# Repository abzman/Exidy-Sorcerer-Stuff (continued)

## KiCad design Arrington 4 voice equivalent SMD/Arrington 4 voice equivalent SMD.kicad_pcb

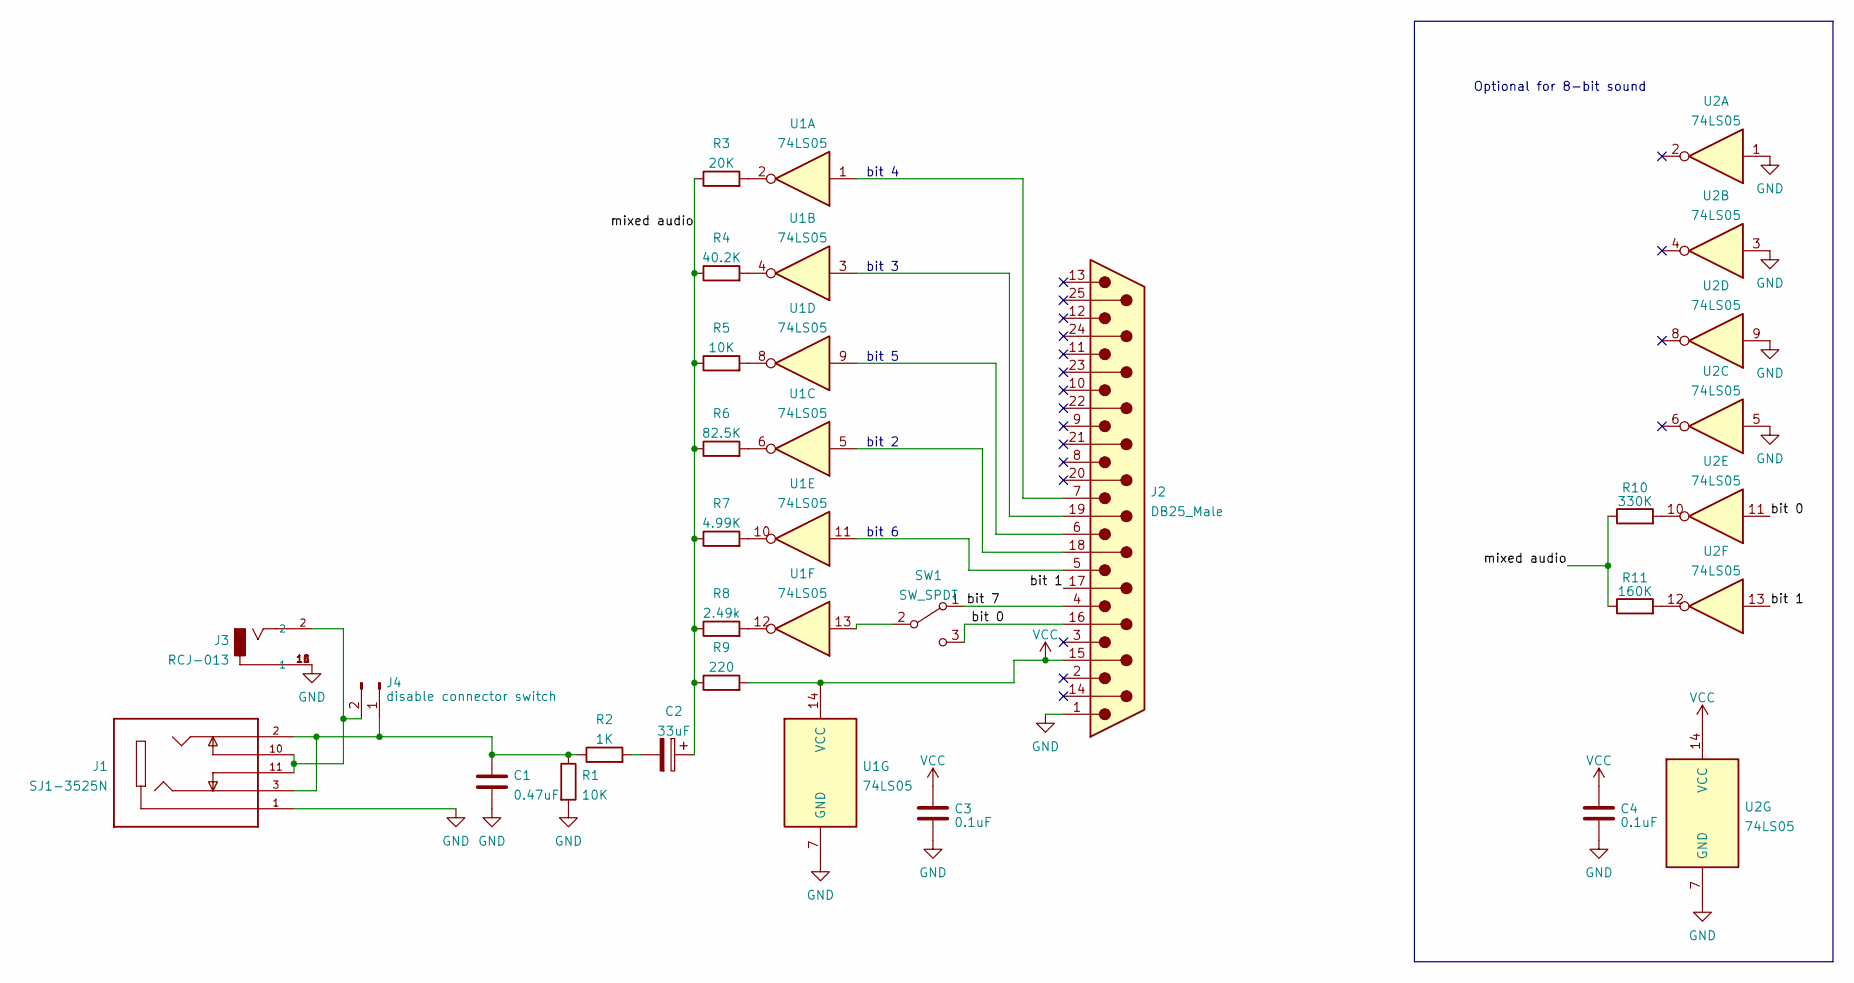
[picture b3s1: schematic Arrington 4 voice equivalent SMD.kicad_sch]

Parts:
C1: 0.47uF; C_0603_1608Metric
C2: 33uF; CP_Radial_D5.0mm_P2.00mm
C3, C4: 0.1uF; C_0603_1608Metric
J1: SJ1-3525N; CUI_SJ1-3525N; PARTREV 1.02
J2: DB25_Male; DSUB-25_Male_EdgeMount_P2.77mm
J3: RCJ-013; CUI_RCJ-013; PART_REV B
J4: disable connector switch; PinHeader_1x02_P2.54mm_Vertical
R1, R5: 10K; R_0603_1608Metric
R2: 1K; R_0603_1608Metric
R3: 20K; R_0603_1608Metric
R4: 40.2K; R_0603_1608Metric
R6: 82.5K; R_0603_1608Metric
R7: 4.99K; R_0603_1608Metric
R8: 2.49k; R_0603_1608Metric
R9: 220; R_0603_1608Metric
R10: 330K; R_0603_1608Metric
R11: 160K; R_0603_1608Metric
SW1: SW_SPDT; PinHeader_1x03_P2.54mm_Vertical
U1, U2: 74LS05; SO-14_3.9x8.65mm_P1.27mm

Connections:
/bit 0: J2.16, SW1.3 (C), U2.11
/bit 1: J2.17, U2.13
/bit 7: J2.4, SW1.1 (A)
/mixed audio: C2.1, R3.1, R4.1, R5.1, R6.1, R7.1, R8.1, R9.1, R10.1, R11.1
GND: C1.2, C3.2, C4.2, J1.1, J2.1, J3.1A (1), J3.1B (1), J3.1C (1), R1.2, U1.7 (GND), U2.1, U2.3, U2.5, U2.7 (GND), U2.9
unnamed: C2.2, R2.2
unnamed: J2.18, U1.5
unnamed: J2.19, U1.3
unnamed: J2.5, U1.11
unnamed: J2.6, U1.9
unnamed: J2.7, U1.1
unnamed: C1.1, J1.2, J1.3, J4.1, R1.1, R2.1
unnamed: J1.10, J1.11, J3.2, J4.2
unnamed: R3.2, U1.2
unnamed: R4.2, U1.4
unnamed: R5.2, U1.8
unnamed: R6.2, U1.6
unnamed: R7.2, U1.10
unnamed: R8.2, U1.12
unnamed: R10.2, U2.10
unnamed: R11.2, U2.12
unnamed: SW1.2 (B), U1.13
VCC: C3.1, C4.1, J2.15, R9.2, U1.14 (VCC), U2.14 (VCC)

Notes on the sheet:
Optional for 8-bit sound
bit 2
bit 5
bit 4
bit 6
bit 3

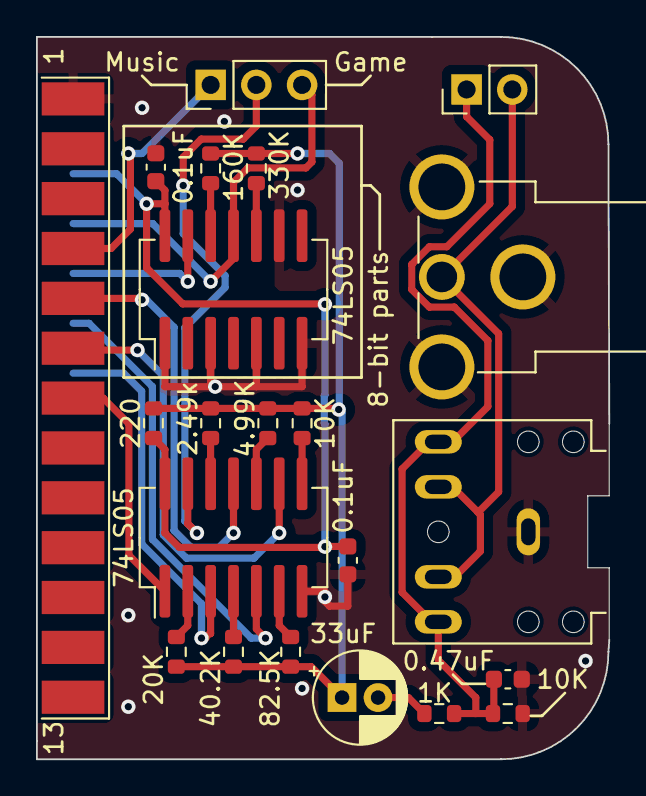
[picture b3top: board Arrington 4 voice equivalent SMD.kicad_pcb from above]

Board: 2 copper layers, 31.8 x 40.1 mm, 22 parts (0 on the bottom side), 23 nets.

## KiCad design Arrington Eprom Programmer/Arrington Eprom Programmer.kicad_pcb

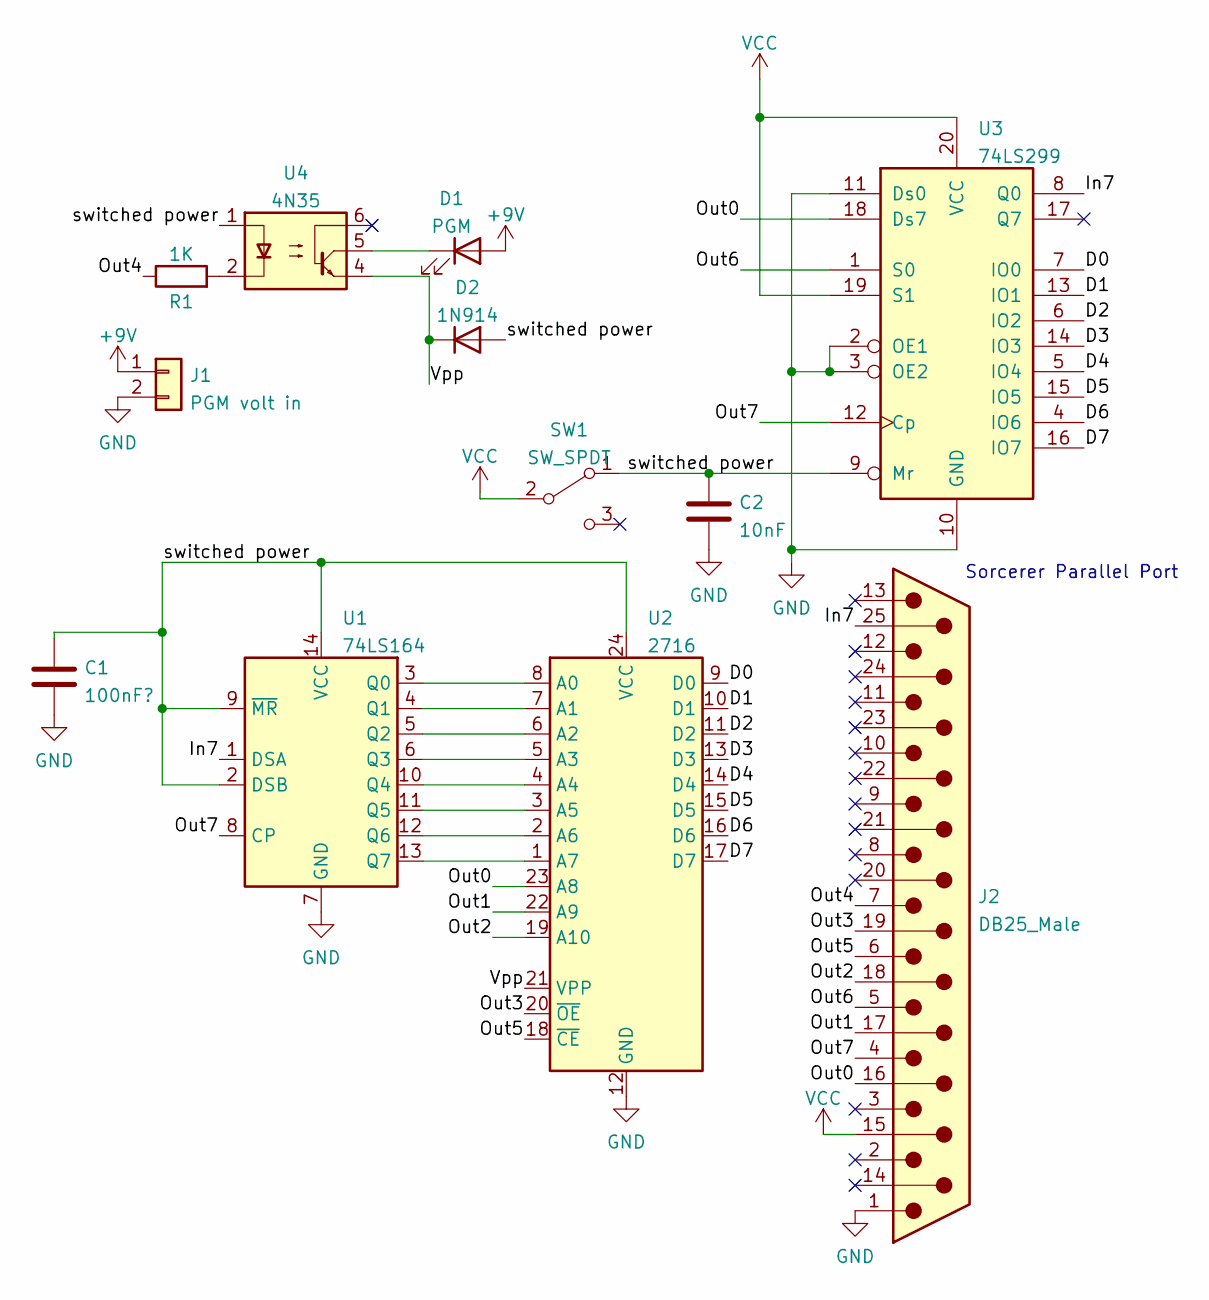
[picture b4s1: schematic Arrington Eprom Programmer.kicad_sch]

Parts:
C1: 100nF?; C_Rect_L9.0mm_W2.5mm_P7.50mm_MKT
C2: 10nF; C_Rect_L9.0mm_W2.5mm_P7.50mm_MKT
D1: PGM; LED_D3.0mm
D2: 1N914; D_DO-35_SOD27_P7.62mm_Horizontal
J1: PGM volt in; PinHeader_1x02_P2.54mm_Vertical
J2: DB25_Male; DSUB-25_Male_EdgeMount_P2.77mm
R1: 1K; R_Axial_DIN0207_L6.3mm_D2.5mm_P10.16mm_Horizontal
SW1: SW_SPDT; PinHeader_1x03_P2.54mm_Vertical
U1: 74LS164; DIP-14_W7.62mm
U2: 2716; DIP-24_W15.24mm
U3: 74LS299; DIP-20_W7.62mm
U4: 4N35; DIP-6_W7.62mm

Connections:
+9V: D1.2 (A), J1.1
/D0: U2.9 (D0), U3.7 (IO0)
/D1: U2.10 (D1), U3.13 (IO1)
/D2: U2.11 (D2), U3.6 (IO2)
/D3: U2.13 (D3), U3.14 (IO3)
/D4: U2.14 (D4), U3.5 (IO4)
/D5: U2.15 (D5), U3.15 (IO5)
/D6: U2.16 (D6), U3.4 (IO6)
/D7: U2.17 (D7), U3.16 (IO7)
/In7: J2.25, U1.1 (DSA), U3.8 (Q0)
/Out0: J2.16, U2.23 (A8), U3.18 (Ds7)
/Out1: J2.17, U2.22 (A9)
/Out2: J2.18, U2.19 (A10)
/Out3: J2.19, U2.20 (~OE)
/Out4: J2.7, R1.1
/Out5: J2.6, U2.18 (~CE)
/Out6: J2.5, U3.1 (S0)
/Out7: J2.4, U1.8 (CP), U3.12 (Cp)
/Vpp: D2.1 (K), U2.21 (VPP), U4.4
/switched power: C1.1, C2.1, D2.2 (A), SW1.1 (A), U1.2 (DSB), U1.9 (~MR), U1.14 (VCC), U2.24 (VCC), U3.9 (Mr), U4.1
GND: C1.2, C2.2, J1.2, J2.1, U1.7 (GND), U2.12 (GND), U3.2 (OE1), U3.3 (OE2), U3.10 (GND), U3.11 (Ds0)
unnamed: D1.1 (K), U4.5
unnamed: R1.2, U4.2
unnamed: U1.3 (Q0), U2.8 (A0)
unnamed: U1.4 (Q1), U2.7 (A1)
unnamed: U1.5 (Q2), U2.6 (A2)
unnamed: U1.6 (Q3), U2.5 (A3)
unnamed: U1.10 (Q4), U2.4 (A4)
unnamed: U1.11 (Q5), U2.3 (A5)
unnamed: U1.12 (Q6), U2.2 (A6)
unnamed: U1.13 (Q7), U2.1 (A7)
VCC: J2.15, SW1.2 (B), U3.19 (S1), U3.20 (VCC)

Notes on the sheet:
Sorcerer Parallel Port

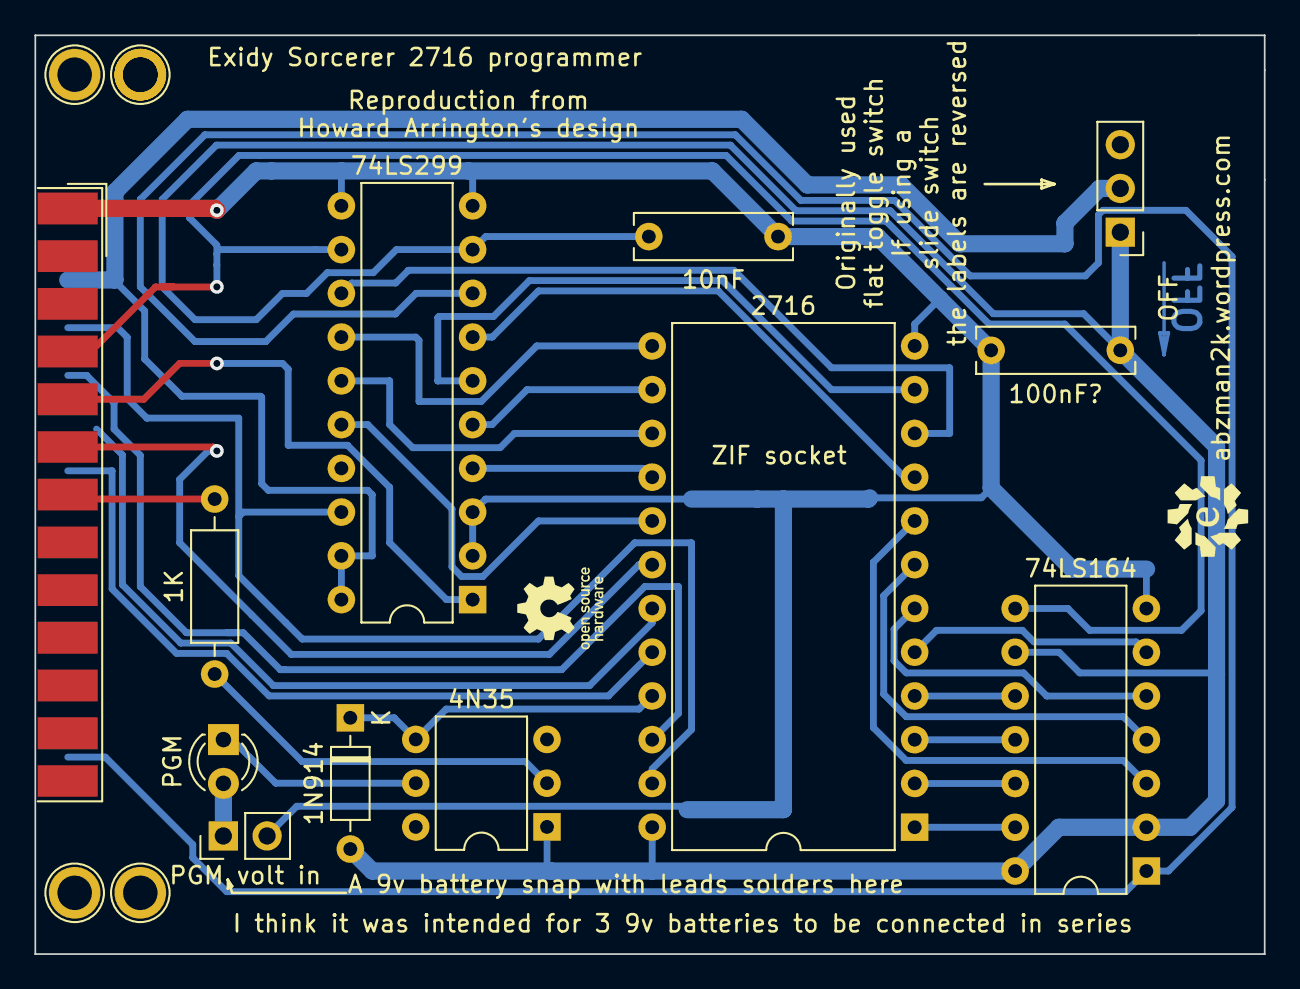
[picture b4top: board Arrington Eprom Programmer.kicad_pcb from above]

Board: 2 copper layers, 71.4 x 53.3 mm, 12 parts (0 on the bottom side), 32 nets.

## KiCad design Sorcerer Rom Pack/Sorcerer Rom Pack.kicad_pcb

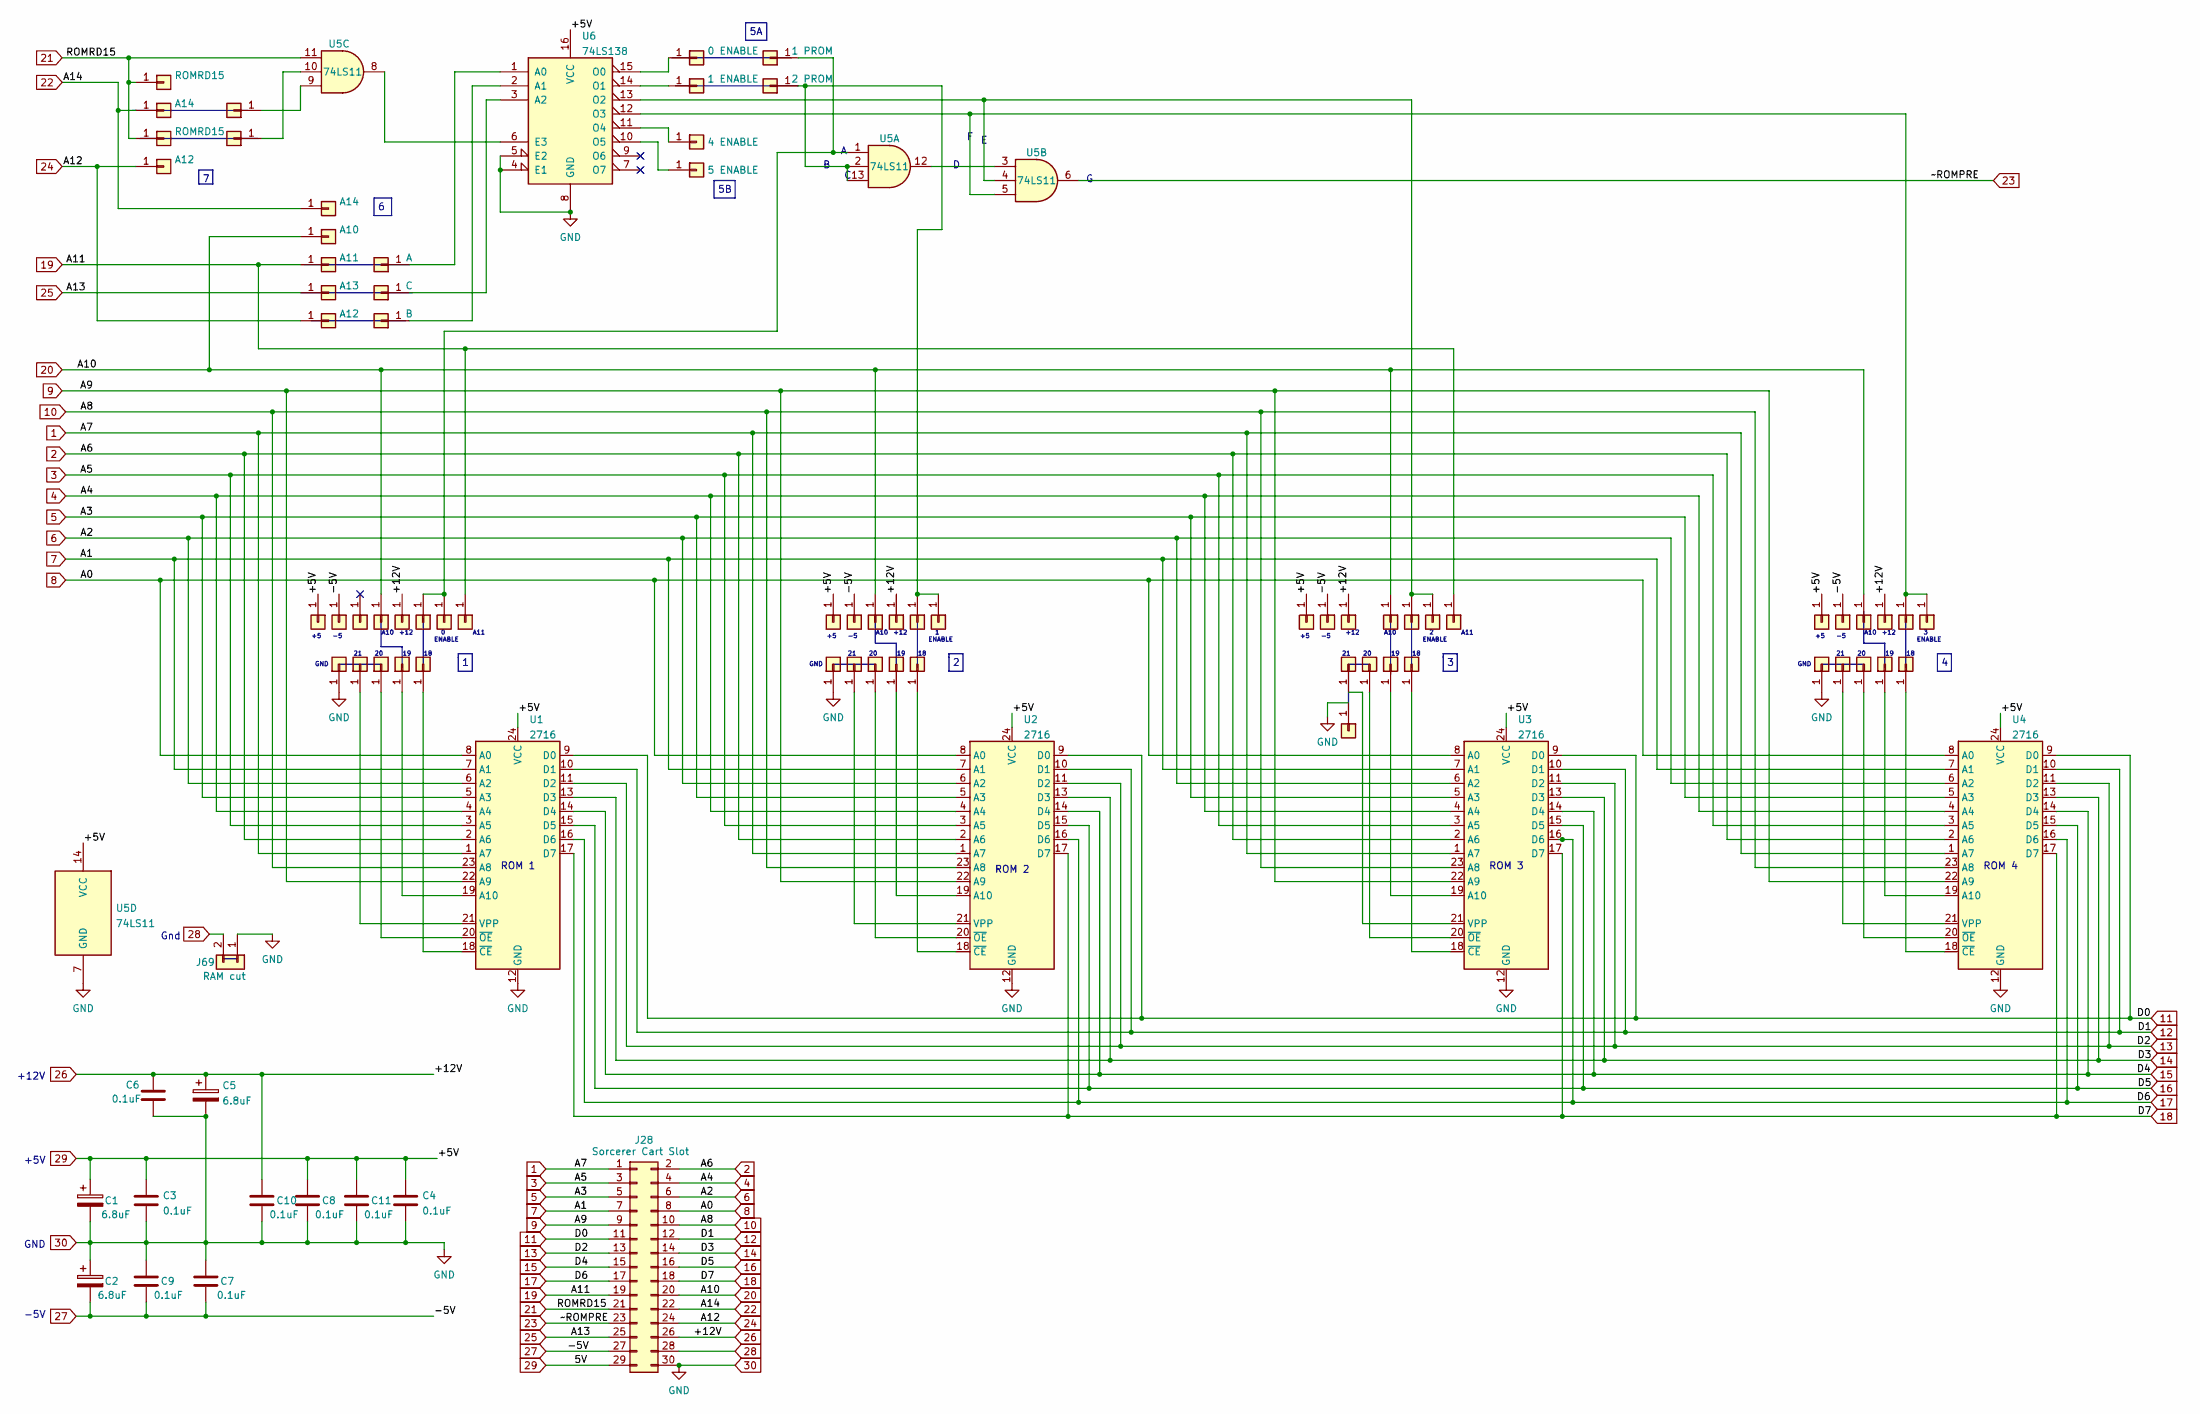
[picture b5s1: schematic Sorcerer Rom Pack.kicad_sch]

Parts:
C1, C2, C5: 6.8uF; CP_Radial_Tantal_D4.5mm_P5.00mm
C3, C4, C6, C7, C8, C9, C10, C11: 0.1uF; C_Disc_D4.3mm_W1.9mm_P5.00mm
J1, J3: ROMRD15; PinHeader_1x01_P2.54mm_Vertical
J2, J8: A14; PinHeader_1x01_P2.54mm_Vertical
J4, J12: A12; PinHeader_1x01_P2.54mm_Vertical
J5, J6: Conn_01x01; PinHeader_1x01_P2.54mm_Vertical
J7, J13, J14, J15, J16, J17, J20, J21, J22, J23, J24, J25, J26, J27, J35, J36, J37, J38, J39, J40, J41, J42, J43, J44, J45, J46, J47, J48, J49, J50, J51, J52, J53, J54, J55, J56, J57, J58, J59, J60, J61, J62, J63, J64, J65, J66, J67, J68: A; PinHeader_1x01_P2.54mm_Vertical
J9: A10; PinHeader_1x01_P2.54mm_Vertical
J10: A11; PinHeader_1x01_P2.54mm_Vertical
J11: A13; PinHeader_1x01_P2.54mm_Vertical
J18: C; PinHeader_1x01_P2.54mm_Vertical
J19: B; PinHeader_1x01_P2.54mm_Vertical
J28: Sorcerer Cart Slot; edge mounted 30 pin card edge connector (2x15 pin)
J29: 0 ENABLE; PinHeader_1x01_P2.54mm_Vertical
J30: 1 ENABLE; PinHeader_1x01_P2.54mm_Vertical
J31: 4 ENABLE; PinHeader_1x01_P2.54mm_Vertical
J32: 5 ENABLE; PinHeader_1x01_P2.54mm_Vertical
J33: 1 PROM; PinHeader_1x01_P2.54mm_Vertical
J34: 2 PROM; PinHeader_1x01_P2.54mm_Vertical
J69: RAM cut; SolderJumper-2_P1.3mm_Open_RoundedPad1.0x1.5mm
U1, U2, U3, U4: 2716; DIP-24_W15.24mm
U5: 74LS11; DIP-14_W7.62mm
U6: 74LS138; DIP-16_W7.62mm

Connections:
1: J28.1, U1.1 (A7), U2.1 (A7), U3.1 (A7), U4.1 (A7)
2: J28.2, U1.2 (A6), U2.2 (A6), U3.2 (A6), U4.2 (A6)
3: J28.3, U1.3 (A5), U2.3 (A5), U3.3 (A5), U4.3 (A5)
4: J28.4, U1.4 (A4), U2.4 (A4), U3.4 (A4), U4.4 (A4)
5: J28.5, U1.5 (A3), U2.5 (A3), U3.5 (A3), U4.5 (A3)
6: J28.6, U1.6 (A2), U2.6 (A2), U3.6 (A2), U4.6 (A2)
7: J28.7, U1.7 (A1), U2.7 (A1), U3.7 (A1), U4.7 (A1)
8: J28.8, U1.8 (A0), U2.8 (A0), U3.8 (A0), U4.8 (A0)
9: J28.9, U1.22 (A9), U2.22 (A9), U3.22 (A9), U4.22 (A9)
10: J28.10, U1.23 (A8), U2.23 (A8), U3.23 (A8), U4.23 (A8)
11: J28.11, U1.9 (D0), U2.9 (D0), U3.9 (D0), U4.9 (D0)
12: J28.12, U1.10 (D1), U2.10 (D1), U3.10 (D1), U4.10 (D1)
13: J28.13, U1.11 (D2), U2.11 (D2), U3.11 (D2), U4.11 (D2)
14: J28.14, U1.13 (D3), U2.13 (D3), U3.13 (D3), U4.13 (D3)
15: J28.15, U1.14 (D4), U2.14 (D4), U3.14 (D4), U4.14 (D4)
16: J28.16, U1.15 (D5), U2.15 (D5), U3.15 (D5), U4.15 (D5)
17: J28.17, U1.16 (D6), U2.16 (D6), U3.16 (D6), U4.16 (D6)
18: J28.18, U1.17 (D7), U2.17 (D7), U3.17 (D7), U4.17 (D7)
19: J10.1, J27.1, J28.19, J57.1
20: J9.1, J20.1, J28.20, J39.1, J52.1, J62.1
21: J1.1, J3.1, J28.21, U5.11
22: J2.1, J8.1, J28.22
23: J28.23, U5.6
24: J4.1, J12.1, J28.24
25: J11.1, J28.25
26: C5.1, C6.1, C10.1, J22.1, J28.26, J41.1, J48.1, J64.1
27: C2.2, C7.2, C9.2, J13.1, J28.27, J37.1, J47.1, J60.1
28: J28.28, J69.2
29: C1.1, C3.1, C4.1, C8.1, C11.1, J7.1, J28.29, J35.1, J46.1, J58.1, U1.24 (VCC), U2.24 (VCC), U3.24 (VCC), U4.24 (VCC), U5.14 (VCC), U6.16 (VCC)
30: C1.2, C2.1, C3.2, C4.2, C5.2, C6.2, C7.1, C8.2, C9.1, C10.2, C11.2, J14.1, J28.30, J36.1, J50.1, J59.1, J69.1, U1.12 (GND), U2.12 (GND), U3.12 (GND), U4.12 (GND), U5.7 (GND), U6.4 (E1), U6.5 (E2), U6.8 (GND)
unnamed: J5.1, U5.9
unnamed: J6.1, U5.10
unnamed: J16.1, U1.21 (VPP)
unnamed: J17.1, U6.1 (A0)
unnamed: J18.1, U6.3 (A2)
unnamed: J19.1, U6.2 (A1)
unnamed: J21.1, U1.20 (~OE)
unnamed: J23.1, U1.19 (A10)
unnamed: J24.1, J26.1, J33.1, U5.1
unnamed: J25.1, U1.18 (~CE)
unnamed: J29.1, U6.15 (O0)
unnamed: J30.1, U6.14 (O1)
unnamed: J31.1, U6.11 (O4)
unnamed: J32.1, U6.10 (O5)
unnamed: J34.1, J43.1, J45.1, U5.2, U5.13
unnamed: J38.1, U2.21 (VPP)
unnamed: J40.1, U2.20 (~OE)
unnamed: J42.1, U2.19 (A10)
unnamed: J44.1, U2.18 (~CE)
unnamed: J49.1, U3.21 (VPP)
unnamed: J51.1, U3.20 (~OE)
unnamed: J53.1, U3.19 (A10)
unnamed: J54.1, J56.1, U5.4, U6.13 (O2)
unnamed: J55.1, U3.18 (~CE)
unnamed: J61.1, U4.21 (VPP)
unnamed: J63.1, U4.20 (~OE)
unnamed: J65.1, U4.19 (A10)
unnamed: J66.1, J68.1, U5.5, U6.12 (O3)
unnamed: J67.1, U4.18 (~CE)
unnamed: U5.8, U6.6 (E3)
unnamed: U5.3, U5.12

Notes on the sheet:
+12
+5V
-5V
A11
0 ENABLE
A10
ROM 4
GND
1 ENABLE
Gnd
3 ENABLE
ROM 3
+12V
ROM 2
ROM 1
2 ENABLE

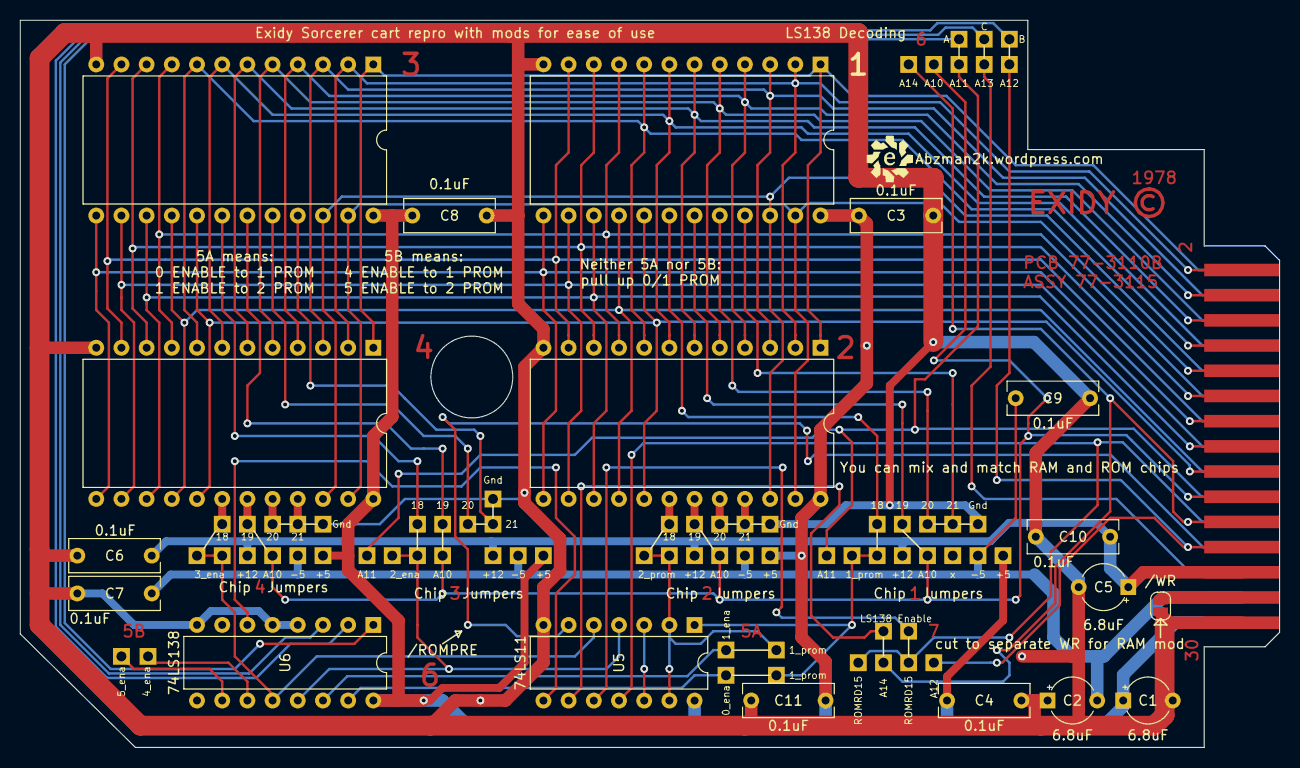
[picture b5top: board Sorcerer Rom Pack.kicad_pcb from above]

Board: 2 copper layers, 127.0 x 73.3 mm, 86 parts (0 on the bottom side), 61 nets.

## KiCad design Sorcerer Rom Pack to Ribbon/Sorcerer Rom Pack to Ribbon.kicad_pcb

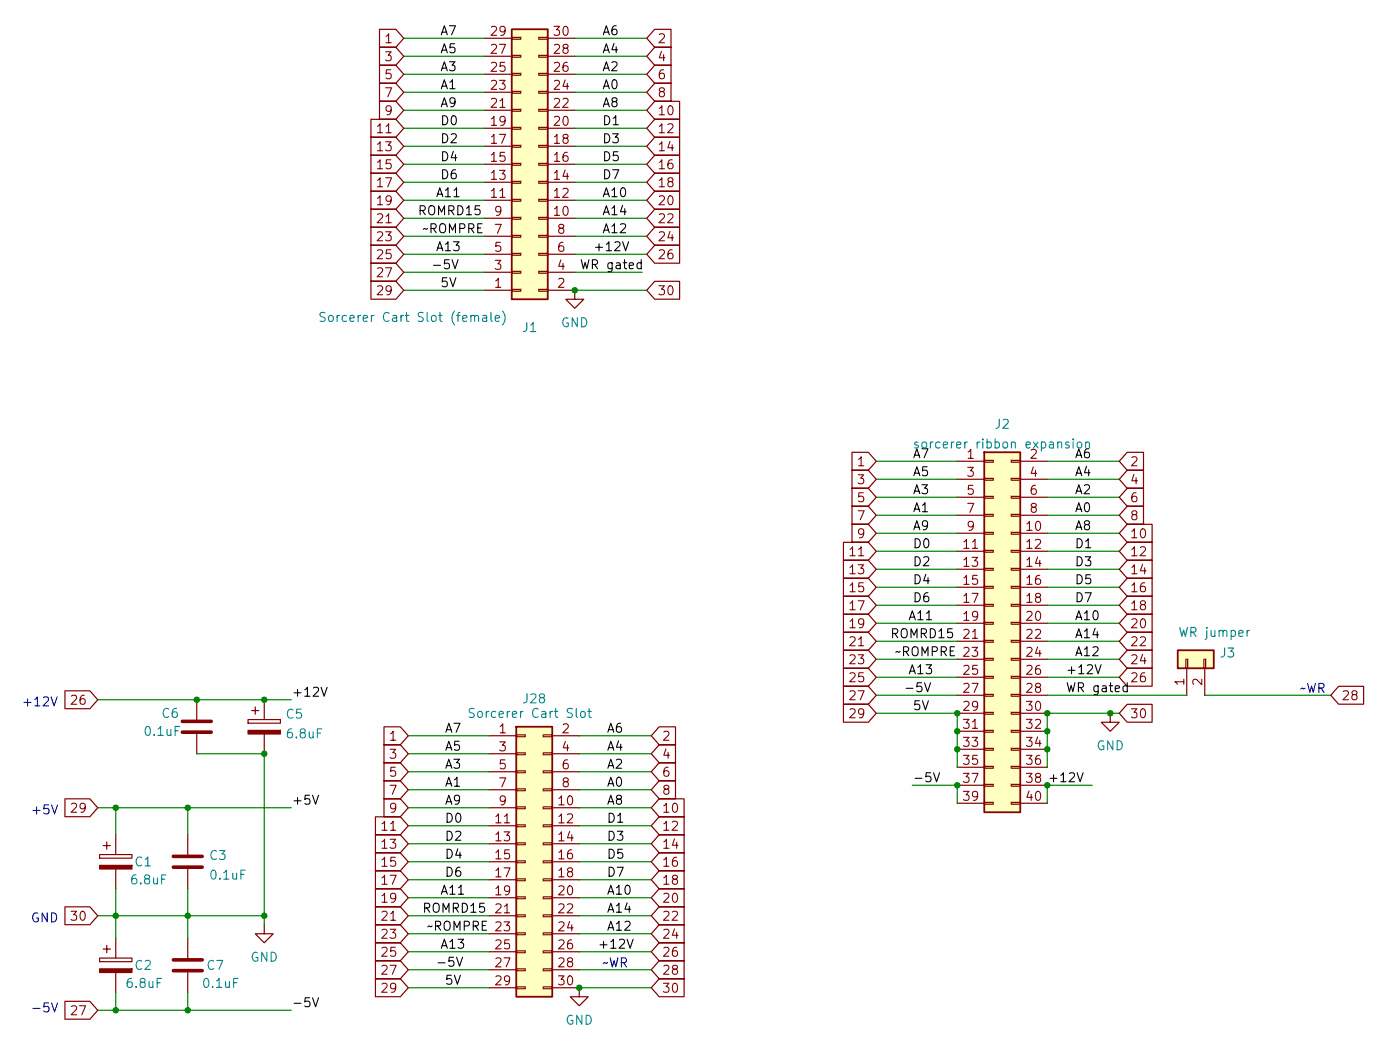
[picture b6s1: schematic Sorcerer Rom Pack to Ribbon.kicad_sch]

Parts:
C1, C2, C5: 6.8uF; CP_Radial_Tantal_D4.5mm_P5.00mm
C3, C6, C7: 0.1uF; C_Disc_D4.3mm_W1.9mm_P5.00mm
J1: Sorcerer Cart Slot (female); edge mounted 30 pin card edge connector (2x15 pin)
J2: sorcerer ribbon expansion; PinHeader_2x20_P2.54mm_Vertical
J3: WR jumper; SolderJumper-2_P1.3mm_Open_RoundedPad1.0x1.5mm
J28: Sorcerer Cart Slot; edge mounted 30 pin card edge connector (2x15 pin)

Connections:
1: J1.29, J2.1, J28.1
2: J1.30, J2.2, J28.2
3: J1.27, J2.3, J28.3
4: J1.28, J2.4, J28.4
5: J1.25, J2.5, J28.5
6: J1.26, J2.6, J28.6
7: J1.23, J2.7, J28.7
8: J1.24, J2.8, J28.8
9: J1.21, J2.9, J28.9
10: J1.22, J2.10, J28.10
11: J1.19, J2.11, J28.11
12: J1.20, J2.12, J28.12
13: J1.17, J2.13, J28.13
14: J1.18, J2.14, J28.14
15: J1.15, J2.15, J28.15
16: J1.16, J2.16, J28.16
17: J1.13, J2.17, J28.17
18: J1.14, J2.18, J28.18
19: J1.11, J2.19, J28.19
20: J1.12, J2.20, J28.20
21: J1.9, J2.21, J28.21
22: J1.10, J2.22, J28.22
23: J1.7, J2.23, J28.23
24: J1.8, J2.24, J28.24
25: J1.5, J2.25, J28.25
26: C5.1, C6.1, J1.6, J2.26, J2.38, J2.40, J28.26
27: C2.2, C7.2, J1.3, J2.27, J2.37, J2.39, J28.27
28: J3.2, J28.28
29: C1.1, C3.1, J1.1, J2.29, J2.31, J2.33, J2.35, J28.29
30: C1.2, C2.1, C3.2, C5.2, C6.2, C7.1, J1.2, J2.30, J2.32, J2.34, J2.36, J28.30
/WR gated: J1.4, J2.28, J3.1

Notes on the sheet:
+5V
-5V
~WR
+12V
GND

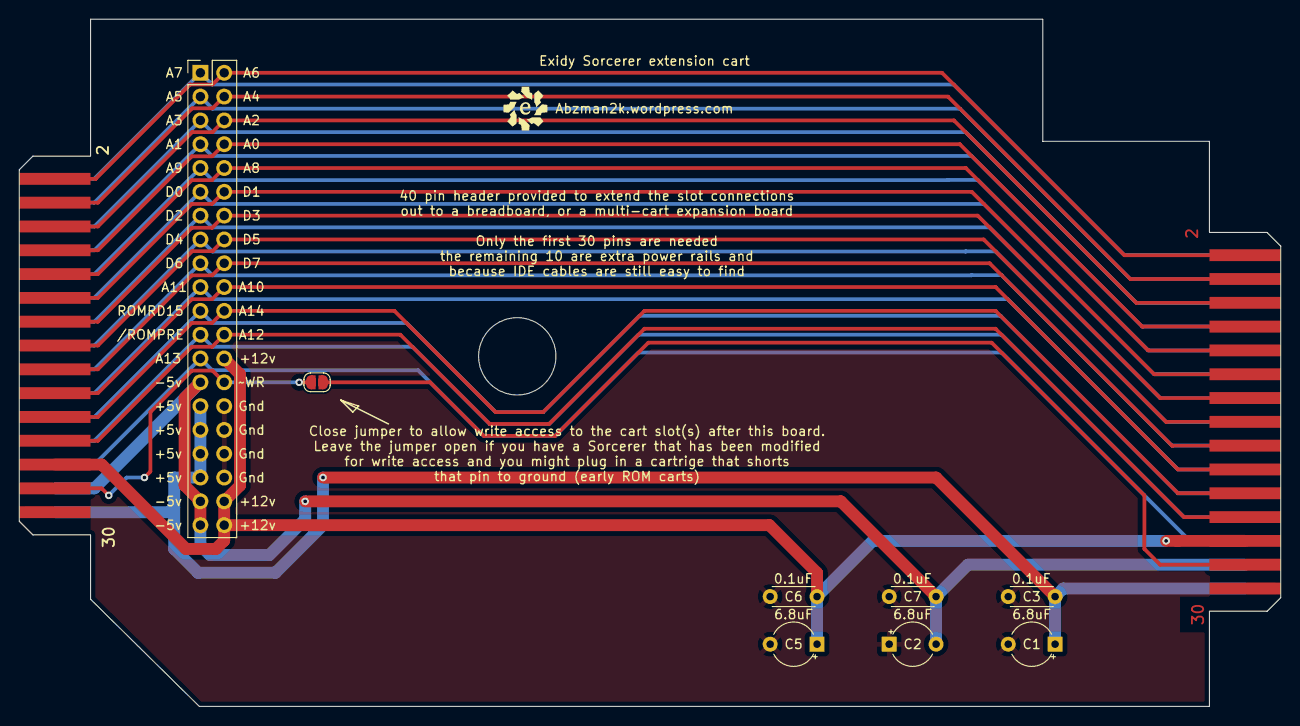
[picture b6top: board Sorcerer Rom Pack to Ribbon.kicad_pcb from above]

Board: 2 copper layers, 134.6 x 73.3 mm, 10 parts (0 on the bottom side), 31 nets.

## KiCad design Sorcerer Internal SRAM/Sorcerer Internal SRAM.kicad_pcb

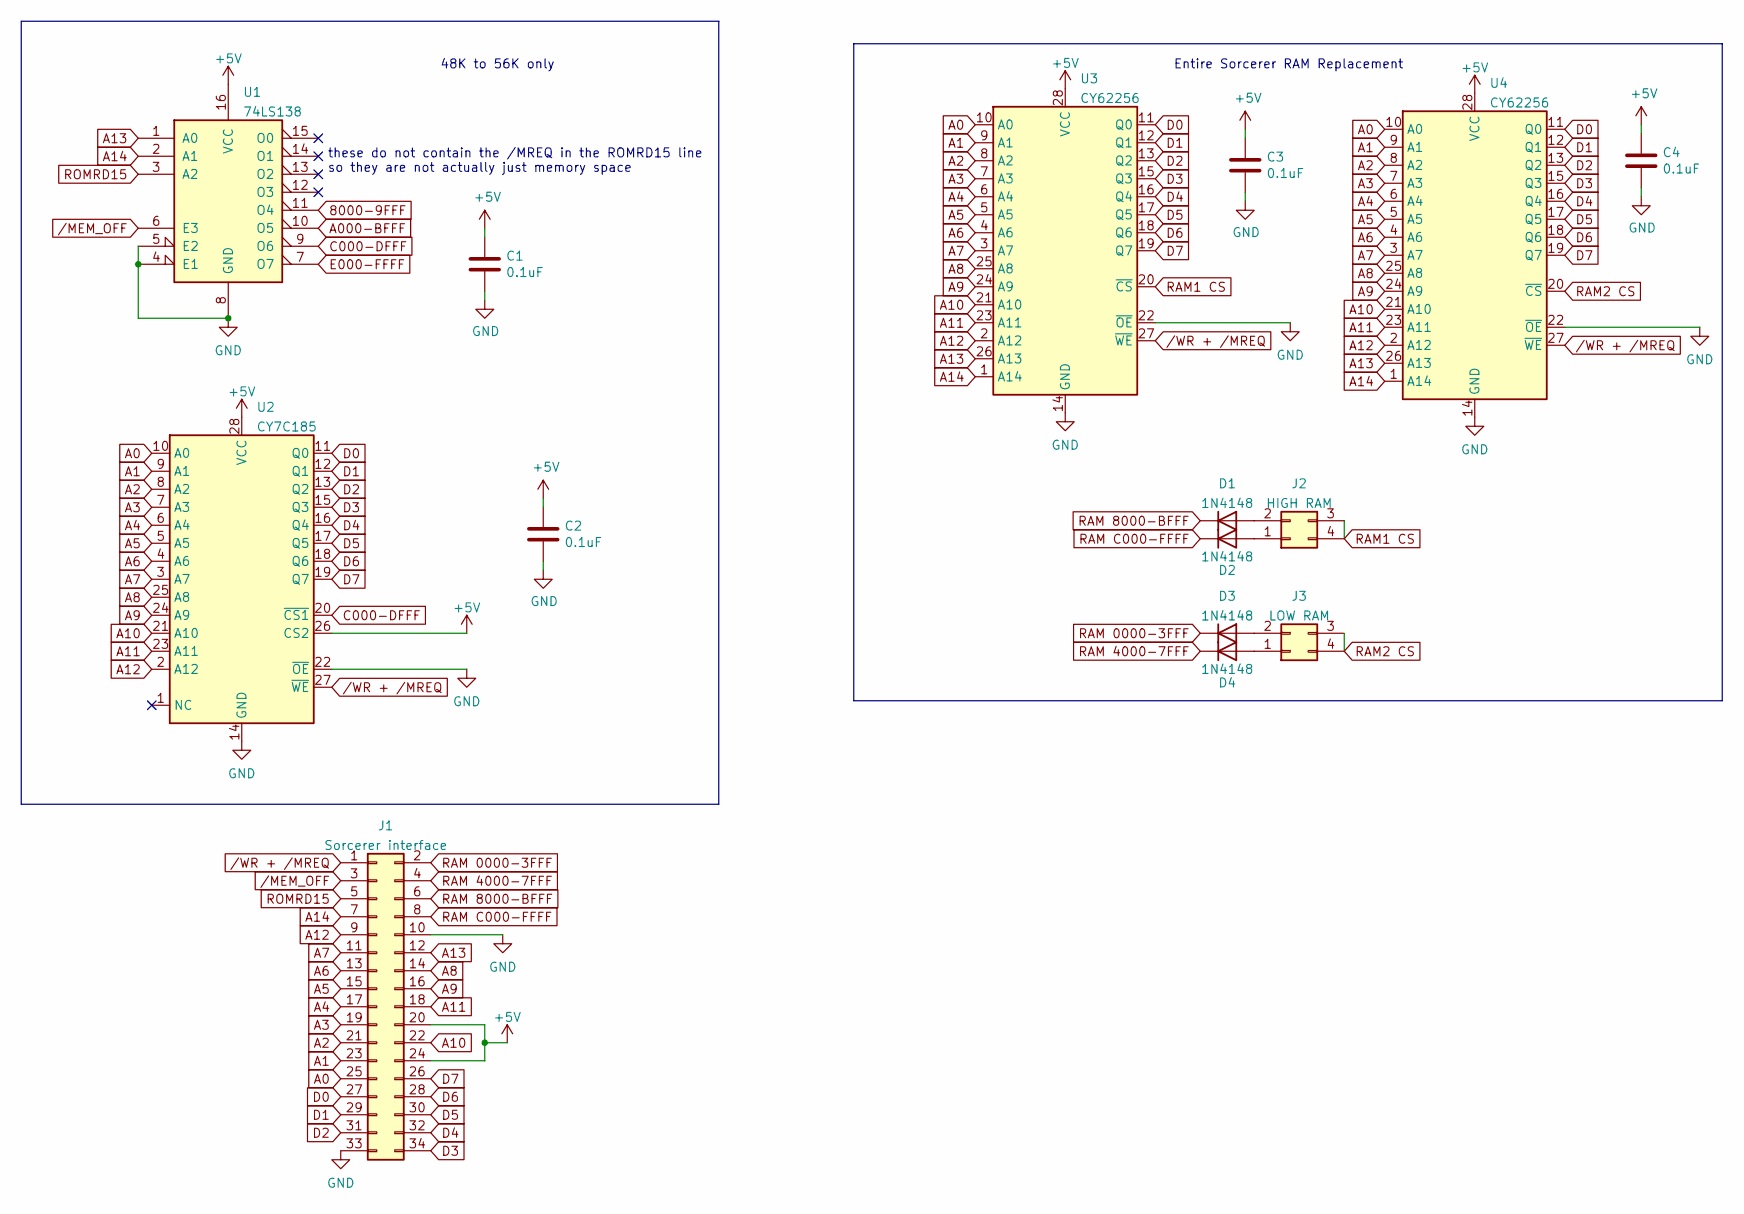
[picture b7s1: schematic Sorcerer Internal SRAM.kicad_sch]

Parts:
C1, C2, C3, C4: 0.1uF; C_Axial_L3.8mm_D2.6mm_P7.50mm_Horizontal
D1, D2, D3, D4: 1N4148; D_DO-35_SOD27_P2.54mm_Vertical_KathodeUp
J1: Sorcerer interface; PinHeader_2x17_P2.54mm_Vertical
J2: HIGH RAM; PinHeader_2x02_P2.54mm_Vertical
J3: LOW RAM; PinHeader_2x02_P2.54mm_Vertical
U1: 74LS138; DIP-16_W7.62mm
U2: CY7C185; DIP-28_W7.62mm
U3, U4: CY62256; DIP-28_W7.62mm

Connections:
8000-9FFF: U1.11 (O4)
+5V: C1.1, C2.1, C3.1, C4.1, J1.20, J1.24, U1.16 (VCC), U2.26 (CS2), U2.28 (VCC), U3.28 (VCC), U4.28 (VCC)
A0: J1.25, U2.10 (A0), U3.10 (A0), U4.10 (A0)
A000-BFFF: U1.10 (O5)
A1: J1.23, U2.9 (A1), U3.9 (A1), U4.9 (A1)
A2: J1.21, U2.8 (A2), U3.8 (A2), U4.8 (A2)
A3: J1.19, U2.7 (A3), U3.7 (A3), U4.7 (A3)
A4: J1.17, U2.6 (A4), U3.6 (A4), U4.6 (A4)
A5: J1.15, U2.5 (A5), U3.5 (A5), U4.5 (A5)
A6: J1.13, U2.4 (A6), U3.4 (A6), U4.4 (A6)
A7: J1.11, U2.3 (A7), U3.3 (A7), U4.3 (A7)
A8: J1.14, U2.25 (A8), U3.25 (A8), U4.25 (A8)
A9: J1.16, U2.24 (A9), U3.24 (A9), U4.24 (A9)
A10: J1.22, U2.21 (A10), U3.21 (A10), U4.21 (A10)
A11: J1.18, U2.23 (A11), U3.23 (A11), U4.23 (A11)
A12: J1.9, U2.2 (A12), U3.2 (A12), U4.2 (A12)
A13: J1.12, U1.1 (A0), U3.26 (A13), U4.26 (A13)
A14: J1.7, U1.2 (A1), U3.1 (A14), U4.1 (A14)
C000-DFFF: U1.9 (O6), U2.20 (~CS1)
D0: J1.27, U2.11 (Q0), U3.11 (Q0), U4.11 (Q0)
D1: J1.29, U2.12 (Q1), U3.12 (Q1), U4.12 (Q1)
D2: J1.31, U2.13 (Q2), U3.13 (Q2), U4.13 (Q2)
D3: J1.34, U2.15 (Q3), U3.15 (Q3), U4.15 (Q3)
D4: J1.32, U2.16 (Q4), U3.16 (Q4), U4.16 (Q4)
D5: J1.30, U2.17 (Q5), U3.17 (Q5), U4.17 (Q5)
D6: J1.28, U2.18 (Q6), U3.18 (Q6), U4.18 (Q6)
D7: J1.26, U2.19 (Q7), U3.19 (Q7), U4.19 (Q7)
E000-FFFF: U1.7 (O7)
GND: C1.2, C2.2, C3.2, C4.2, J1.10, J1.33, U1.4 (E1), U1.5 (E2), U1.8 (GND), U2.14 (GND), U2.22 (~OE), U3.14 (GND), U3.22 (~OE), U4.14 (GND), U4.22 (~OE)
unnamed: D1.2 (A), J2.2
unnamed: D3.2 (A), J3.2
unnamed: D4.2 (A), J3.1
unnamed: D2.2 (A), J2.1
RAM1 CS: J2.3, J2.4, U3.20 (~CS)
RAM2 CS: J3.3, J3.4, U4.20 (~CS)
RAM 0000-3FFF: D3.1 (K), J1.2
RAM 4000-7FFF: D4.1 (K), J1.4
RAM 8000-BFFF: D1.1 (K), J1.6
RAM C000-FFFF: D2.1 (K), J1.8
ROMRD15: J1.5, U1.3 (A2)
/MEM_OFF: J1.3, U1.6 (E3)
/WR + /MREQ: J1.1, U2.27 (~WE), U3.27 (~WE), U4.27 (~WE)

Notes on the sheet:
Entire Sorcerer RAM Replacement
these do not contain the /MREQ in the ROMRD15 line so they are not actually just memory space
48K to 56K only

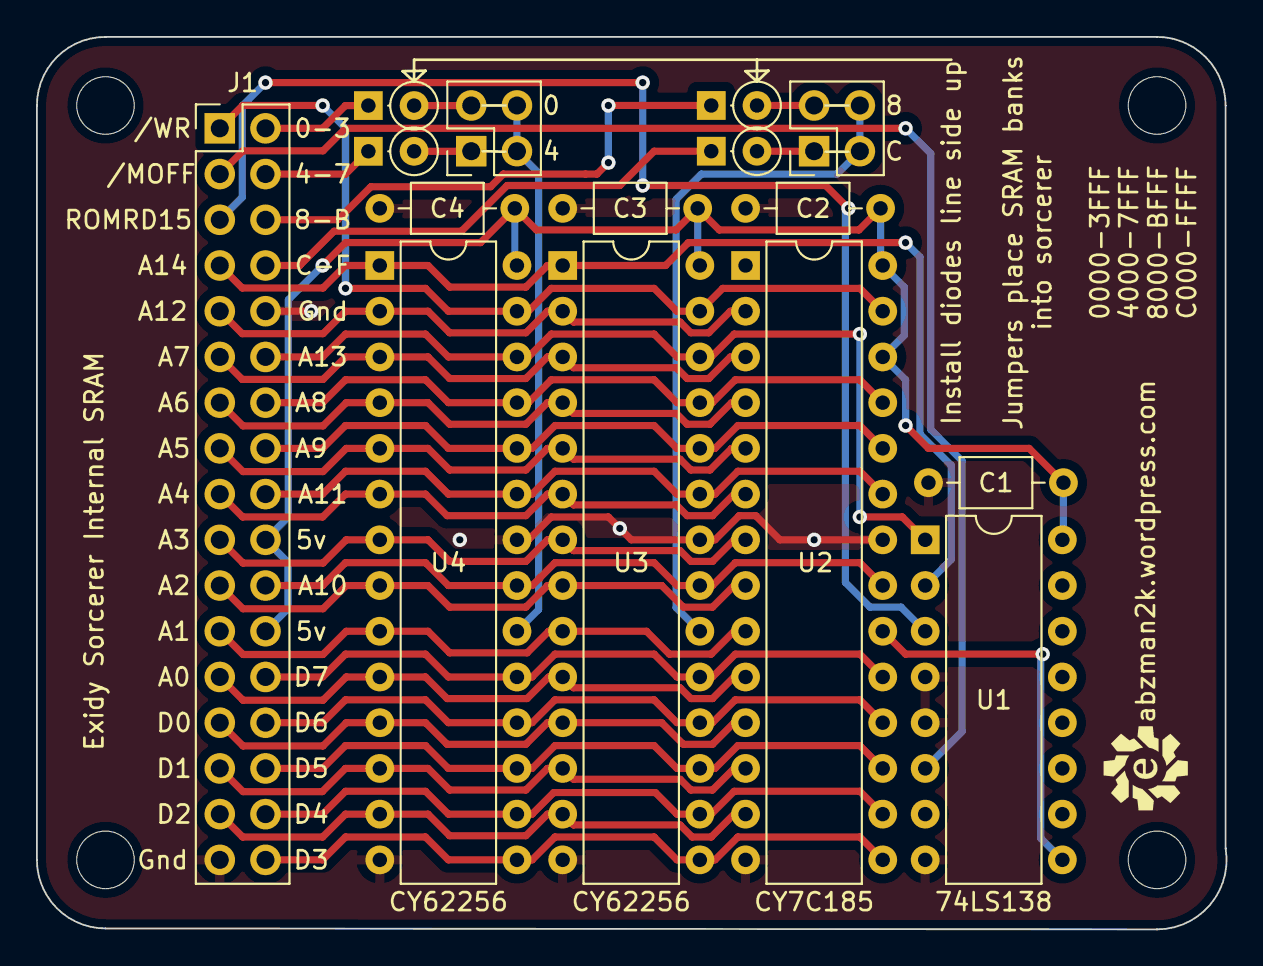
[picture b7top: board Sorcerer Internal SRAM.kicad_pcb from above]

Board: 2 copper layers, 66.1 x 49.6 mm, 15 parts (0 on the bottom side), 39 nets.
